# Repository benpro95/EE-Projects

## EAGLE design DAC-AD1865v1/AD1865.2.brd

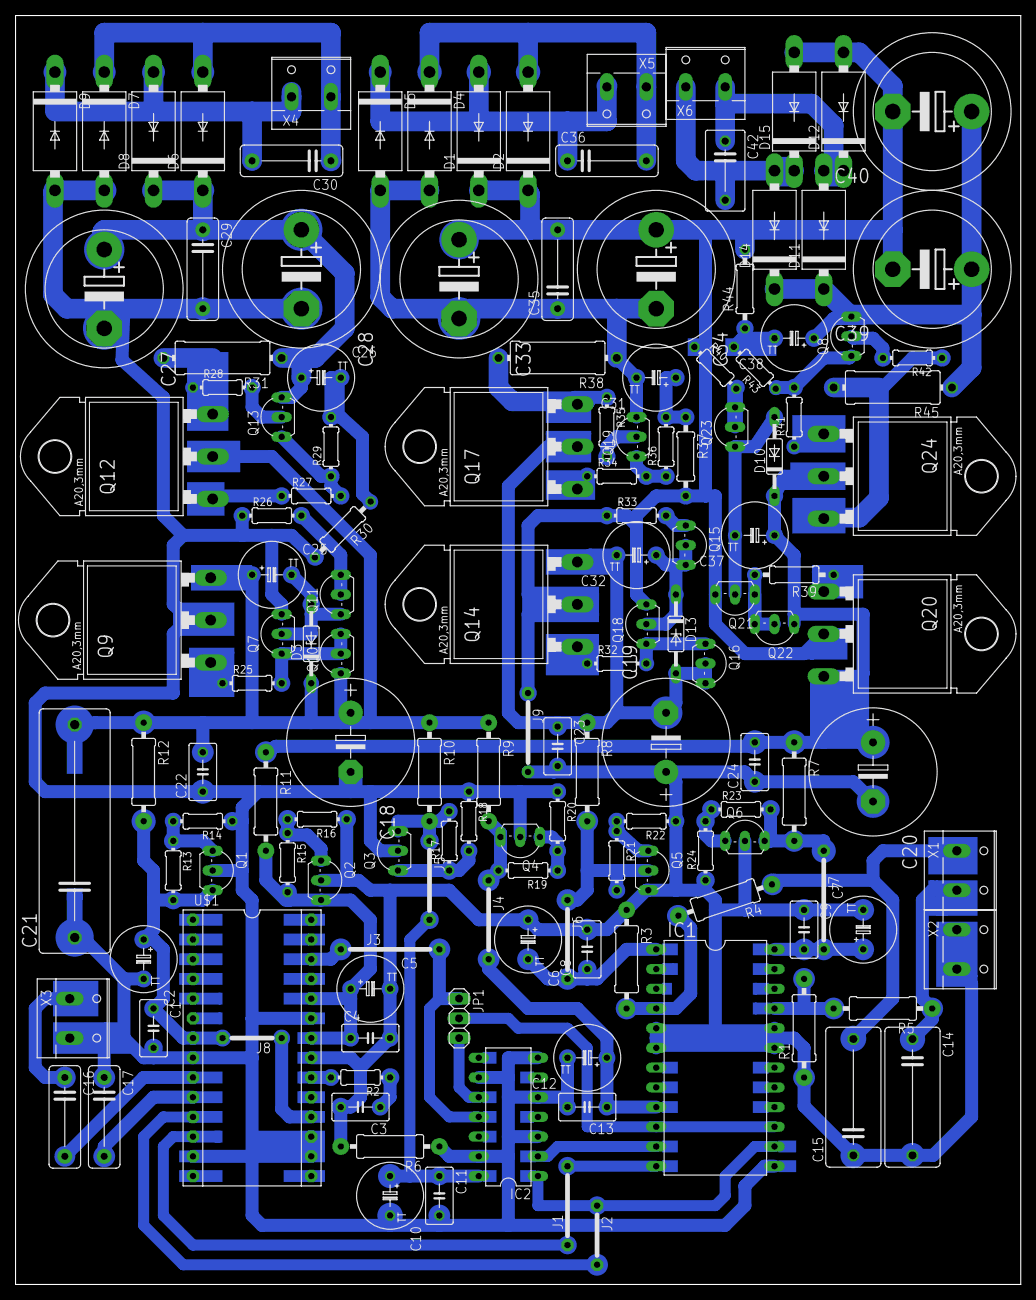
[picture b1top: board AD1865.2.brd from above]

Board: 2 copper layers, 129.5 x 163.5 mm, 144 parts (0 on the bottom side), 77 nets.

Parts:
C1, C3, C4, C8, C9, C11, C13, C22, C23, C24: 68nF; C050-035X075
C2, C5, C6, C7, C10, C12: 47uF; TAP5-80
C14, C15: 10nF; C150-072X183
C16, C17: 10nF; C102-043X133
C18, C19, C20: 100uF; E7,5-16
C21: 1uF; C275-093X316
C25, C26, C31, C32, C37, C38: 100uF; TAP5-80
C27, C28, C33, C34, C39, C40: 2200uF; EB20D
C29, C35: 470nF; C102-043X133
C30, C36: .1; C102-043X133
C42: .1; C075-052X106
D1, D2, D4, D5, D6, D7, D8, D9, D11, D12, D14, D15: 1N5624; DO201-15
D3, D10, D13: 5V6; DO35Z10
IC1: AD1865N-K; DIL24-6
IC2: 74HC04; DIL14
J1, J4, J5, J6, J9: J10MM; 10
J2, J8: J7MM; 07
J3, J7: J12MM; 12
JP1: 1X03
Q1, Q2, Q3, Q4, Q5, Q6: TL431; TO92-EBC
Q7, Q19, Q21: BC550C; TO92-EBC
Q8, Q13, Q18: BC560C; TO92-EBC
Q9, Q12, Q20, Q24: FQA36P15; SOT93
Q10, Q11, Q15, Q16, Q22, Q23: PF5102; TO92-EBC
Q14, Q17: FQA28N15; SOT93
R1, R3: 200R; 0309/12
R2: 470R; 0204/7
R4, R5, R6: 120uH; 0309/12
R7, R8, R9, R10, R11, R12: 10R; 0309/12
R13, R14, R15, R16, R17, R18, R19, R20, R21, R22, R23, R24: 1K; 0204/7
R25, R27, R28, R32, R34, R35, R41, R42: 220R; 0204/7
R26, R33, R40: 10R; 0204/7
R29, R36, R43: 4K7; 0204/7
R30, R37, R44: 4K7; 0207/10
R31, R38, R45: 10R; 0414/15
R39: 220R; 0207/10
U$1: CS8414; DIL28
X1, X2, X3, X4, X5, X6: W237-132

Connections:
0V: C33.+, C34.+, C35.2, C39.-, C40.-, D1.C, D2.C, D12.A, D15.A, J9.1, Q14.C, Q18.E, Q20.C, Q21.E, R33.1, R37.2, R40.1, R44.2
AGND: C3.2, C4.2, C5.-, C6.+, C7.-, C8.2, C9.1, C14.2, C15.1, C19.+, C20.-, C23.2, C24.1, IC1.5, IC1.6, IC1.19, IC1.20, J9.2, Q2.B, Q5.E, Q6.B, R1.1, R3.1, R6.2, R16.1, R22.1, R24.1, U$1.21, X2.1, X2.2
DGND: C1.2, C2.-, C10.-, C11.2, C12.-, C13.2, C17.1, C18.-, C21.1, C22.1, C27.-, C28.-, C29.2, D7.A, D9.A, IC1.13, IC2.3, IC2.5, IC2.7, IC2.9, IC2.13, Q1.B, Q3.B, Q4.B, Q7.E, Q9.C, R6.1, R14.1, R18.1, R20.1, R26.1, R30.2, U$1.8, U$1.13, U$1.16, U$1.17, U$1.23, X3.2
unnamed: R2.2, U$1.20
unnamed: IC1.10, IC1.15, JP1.2
unnamed: C3.1, R2.1
unnamed: IC1.11, IC2.2
unnamed: IC1.14, IC2.1, J2.1
unnamed: J1.1, U$1.12
unnamed: IC1.12, J1.2
unnamed: J2.2, U$1.11
unnamed: IC2.11, J3.2, JP1.1
unnamed: IC2.10, JP1.3
unnamed: J5.1, Q3.E, R10.2, R17.2
unnamed: C19.-, C23.1, C32.-, D13.A, Q14.E, Q16.B, Q16.E, Q17.C, R8.1
unnamed: J3.1, U$1.26
unnamed: C6.-, C8.1, IC1.1, J6.2
unnamed: C7.+, C9.2, IC1.24, J7.2
unnamed: C1.1, C2.+, J8.2, Q1.E, R12.2, R13.2, U$1.7
unnamed: IC1.21, R1.2, R5.2
unnamed: C10.+, C11.1, IC2.14, J5.2
unnamed: IC1.4, R3.2, R4.2
unnamed: C14.1, R5.1, X1.2
unnamed: C15.2, R4.1, X1.1
unnamed: C17.2, U$1.10
unnamed: C16.2, U$1.9
unnamed: C16.1, X3.1
unnamed: C12.+, C13.1, IC1.9, J4.2
unnamed: J7.1, Q6.E, R7.2, R23.2
unnamed: J6.1, Q5.B, R8.2, R21.2
unnamed: Q5.C, R21.1, R22.2
unnamed: J8.1, U$1.18
unnamed: Q1.C, R13.1, R14.2
unnamed: C4.1, C5.+, Q2.E, R11.2, R15.2, U$1.22, U$1.24
unnamed: Q2.C, R15.1, R16.2
unnamed: Q3.C, R17.1, R18.2
unnamed: Q8.B, R42.2
unnamed: Q4.C, R19.1, R20.2
unnamed: Q6.C, R23.1, R24.2
unnamed: C20.+, C24.2, C37.+, D10.C, Q20.E, Q22.C, Q24.C, R7.1, R11.1
unnamed: C18.+, C21.2, C22.2, C25.+, D3.C, Q9.E, Q10.C, Q12.C, R9.1, R10.1, R12.1
unnamed: Q9.B, R25.1
unnamed: Q17.E, R35.1, R38.2
unnamed: Q12.E, R28.1, R31.2
unnamed: Q7.C, Q10.B, Q10.E, R25.2
unnamed: C25.-, D3.A, Q7.B, Q11.C
unnamed: Q11.B, Q11.E, R26.2
unnamed: Q12.B, R27.1
unnamed: Q17.B, R34.1
unnamed: Q13.C, R27.2, R29.1
unnamed: Q13.B, R28.2
unnamed: C26.-, R29.2, R30.1
unnamed: C26.+, C27.+, C28.+, C29.1, D6.C, D8.C, Q13.E, R31.1
unnamed: C30.2, D8.A, D9.C, X4.1
unnamed: C30.1, D6.A, D7.C, X4.2
unnamed: Q19.B, R35.2
unnamed: Q14.B, R32.1
unnamed: Q19.C, R34.2, R36.1
unnamed: Q16.C, Q18.C, R32.2
unnamed: C32.+, D13.C, Q15.B, Q15.E, Q18.B
unnamed: Q15.C, R33.2
unnamed: C31.-, C33.-, C34.-, C35.1, D4.A, D5.A, Q19.E, R38.1
unnamed: C31.+, R36.2, R37.1
unnamed: J4.1, Q4.E, R9.2, R19.2
unnamed: C36.2, D2.A, D4.C, X5.1
unnamed: C36.1, D1.A, D5.C, X5.2
unnamed: Q20.B, R39.1
unnamed: Q21.C, Q22.B, Q22.E, R39.2
unnamed: C37.-, D10.A, Q21.B, Q23.C
unnamed: Q23.B, Q23.E, R40.2
unnamed: Q24.E, R42.1, R45.2
unnamed: Q24.B, R41.1
unnamed: Q8.C, R41.2, R43.1
unnamed: C38.-, R43.2, R44.1
unnamed: C38.+, C39.+, C40.+, D11.C, D14.C, Q8.E, R45.1
unnamed: C42.2, D14.A, D15.C, X6.1
unnamed: C42.1, D11.A, D12.C, X6.2
